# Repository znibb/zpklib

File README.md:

# Znibb's Personal Kicad LIBrary

## Table of Contents <!-- omit from toc -->
- [1. Description](#1-description)
- [2. Setup](#2-setup)
  - [2.1. Inventree](#21-inventree)
  - [2.2. Kicad](#22-kicad)
- [3. Usage](#3-usage)
  - [3.1. Helper scripts](#31-helper-scripts)
  - [3.2. Bulk update Inventree](#32-bulk-update-inventree)
  - [3.3. Adding components to categories](#33-adding-components-to-categories)
  - [3.4. Assemblies](#34-assemblies)
  - [3.5. Releasing a project](#35-releasing-a-project)
  - [3.6. Customizing category symbols](#36-customizing-category-symbols)
- [4. KiCad layer specific usage](#4-kicad-layer-specific-usage)
- [5. EMS Capabilities](#5-ems-capabilities)

## 1. Description
The name of your KiCad symbol libraries will be `LIBRARY_FILE_NAME - TOP_LEVEL_CATEGORY/SUBCATEGORY`, meaning that if your setup is using:

    - Library file name: zpklib.kicad_httplib
    - Inventree top level category name: kicad-parts
    - Subcategory: Resistor

your resistors will show up under a symbol library named `zpklib - kicad-parts/Resistor`

## 2. Setup
### 2.1. Inventree
1. Log into the Inventree web UI and access the Django admin panel by appending `/admin/` to the URL (NOTE the trailing forward slash)
1. Scroll down to `USERS->API Tokens`, click it and then click `ADD API TOKEN +`
1. Take nto of the `Key`, select which `User` the key is for and click `SAVE`

### 2.2. Kicad
1. Create a python venv and install the required packages: `./setup-venv.sh`
1. Create the httplib file: `setup-inventree-httplib.sh`
1. Check that the Inventree server is reachable: `./check_inventree_connection.py`
1. Open the KiCad main window, go to `Preferences->Configure Paths...`
1. Add an `Environment Variable` called `ZPKLIB_DIR` that points to your local library path and click `OK`
1. Go to `Preferences->Manage Symbol Libraries...` and click `Add existing->HTTP (.kicad_httplib)`
1. Select `zpklib.kicad_httplib` and click `Open`

## 3. Usage
### 3.1. Helper scripts
| Name | Usage |
| :--- | :---- |
| check_inventree_connection.py | Verify if httplib is setup correctly |
| create_part.py | Create new Part based on existing component structure |
| next_assembly_ipn.py | Create new EA Part with next IPN in series |
| patch_inventree_structure.py | Compares current `kicad-parts` category state with inventree_structure.yaml and patches the difference in Inventree |
| release_project.py | Handles creation of git tag, github release and upload of relevant assets to said release |
| setup-inventree-httplib.sh | Creates the httplib file used by Kicad to access Inventree |
| setup-venv.sh | Creates a python venv and installs the modules specified in `requirements.txt` |
| update_assembly.py | Update the Inventree Part for the Electronic Assembly |

### 3.2. Bulk update Inventree
1. Source the venv: `. .venv/bin/activate`
1. Analyze the contents of `inventree_structure.yaml` 
1. Applying the structure by running: `./patch_inventree_structure.py`  

### 3.3. Adding components to categories
1. Source the venv: `. .venv/bin/activate`
1. Run `./create_part.py`

### 3.4. Assemblies
1. Source the venv: `. .venv/bin/activate`
1. Reserve an assembly IPN (can be run from any directory): `./next_assembly_ipn.py`. It prompts for the assembly name, creates the part under `electronic-assemblies` and prints the IPN and a link to it
1. In KiCad, go to `Schematic Setup->Project->Text Variables` and add `PART_NUMBER` with the printed IPN
1. Generate the production files, then upload the assembly information (BOM, revision, description and image) to that IPN: `./update_assembly.py PROJECT_DIR`

### 3.5. Releasing a project
1. In the Kicad project, set the `VERSION` and `RELEASE_DATE` text variables, add a `## vX.Y.Z` section to `CHANGELOG.md`, run the production jobset, then commit and push
1. Create the git tag and GitHub release and upload the production files: `./release_project.py PROJECT_DIR`

The script needs `git` and an authenticated `gh`. It aborts if the working tree is dirty, HEAD isn't pushed, or any file name's `_vX.Y.Z_` doesn't match `VERSION`. If the tag or release already exists you are asked before it is overwritten. The uploaded files are set by `FILE_PATTERNS` at the top of the script, and the release notes are the matching `CHANGELOG.md` section.

### 3.6. Customizing category symbols
Kicad handles the default symbol fields `reference, value, footprint, datasheet, description, keywords` in it's own batch, showing `reference` and `value` while hiding the rest by default.  

To hide any of the default fields add:  
```
kicad:
    hide_fields: "FIELD_NAME"
```
to that category in `inventree_structure.yaml`.

The rest of the symbol fields are considered "extra" fields. To make an extra field visible on the symbol add:
```
kivad:
    show_extra_fields: "FIELD_NAME"
```
to that category in `inventree_structure.yaml`.

## 4. KiCad layer specific usage
| Layer | Usage |
| :---- | :---- |
| User.Drawings | PCB/feature dimensions |
| User.Comments | Footprint-specific notes, connector protrusion etc. |
| User.1 / PCB.Comments | PCB comments, stackup details, impedances etc. |

## 5. EMS Capabilities
EMS:
- [JLCPCB](docs/capabilities_JLCPCB.md)

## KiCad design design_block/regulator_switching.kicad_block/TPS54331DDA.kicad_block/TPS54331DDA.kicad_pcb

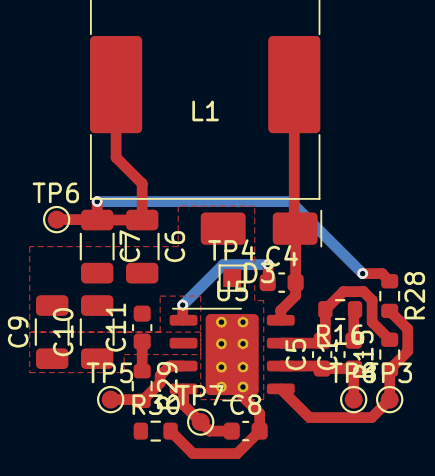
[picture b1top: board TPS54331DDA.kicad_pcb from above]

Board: 4 copper layers, 23 parts (0 on the bottom side), 10 nets.

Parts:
C1: 1n; C_0603_1608Metric
C4: 100n; C_0603_1608Metric
C5: 47p; C_0603_1608Metric
C6, C7: 47u; C_1206_3216Metric
C8: 12n; C_0603_1608Metric
C9, C10: 4.7u; C_1206_3216Metric
C11: 10n; C_0603_1608Metric
D3: B340A-E3-61T; D_SMA
L1: 6.8u; L_12.5x12.5mm_H6.5mm
R15: 3.24k; R_0603_1608Metric
R16: 29.4k; R_0603_1608Metric
R28: 10k; R_0603_1608Metric
R29: 33.2k; R_0603_1608Metric
R30: 8.45k; R_0603_1608Metric
TP3: 3V3_Vsense; TestPoint_Round_D1.0mm
TP4: GND; TestPoint_Square_1.0x1.0mm
TP5: 3V3_EN; TestPoint_Round_D1.0mm
TP6: 3V3; TestPoint_Round_D1.0mm
TP7: 3V3_SS; TestPoint_Round_D1.0mm
TP8: 3V3_COMP; TestPoint_Round_D1.0mm
U5: TPS54331DDAR; SO-8-PowerSOIC_ThermalVias

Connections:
/Regulator 3V3/+3V3: C6.1, C7.1, L1.2, R28.1, TP6.1 (1_1)
/Regulator 3V3/COMP: C1.1, C5.1, TP8.1 (1_1), U5.6 (COMP)
/Regulator 3V3/EN: R29.2, R30.1, TP5.1 (1_1), U5.3 (EN)
/Regulator 3V3/SS: C8.1, TP7.1 (1_1), U5.4 (SS)
/Regulator 3V3/SW: C4.2, D3.1 (K), L1.1, U5.8 (PH)
/Regulator 3V3/V_{IN}: C9.1, C10.1, C11.1, R29.1, U5.2 (V_{IN})
/Regulator 3V3/V_{SENSE}: R15.1, R28.2, TP3.1 (1_1), U5.5 (V_{SENSE})
GND: C5.2, C6.2, C7.2, C8.2, C9.2, C10.2, C11.2, D3.2 (A), R15.2, R16.2, R30.2, TP4.1 (1_1), U5.7 (GND), U5.9 (EPAD)
unnamed: C1.2, R16.1
unnamed: C4.1, U5.1 (BOOT)

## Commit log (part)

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2026-03-12 Set up .gitignore
2026-03-15 Added 0201->1210 footprints for resistors, capacitors and inductors
2026-03-15 Added basic symbols for resistors, capacitors and inductors
2026-03-15 Added tools for local dev instance of inventree
2026-03-15 Updated gitignore
2026-03-15 Updated documentation, WIP
2026-04-01 Deleted obsolete local httplib file
2026-04-01 Added SOIC-16W_7.5x10.3mm_P1.27mm footprint
2026-04-02 Added a generic Symbol parameter handle categories without default symbols
2026-04-02 Added Sensor category
2026-04-02 Changed URL handling to allow handling of other cases than a straight up pdf file
2026-04-04 Added IPC-7354 reference document
2026-04-04 Added Switch category
2026-04-04 Added C&K PTS645VH83 mom push switch
2026-04-04 Added option to enter Value as blank to re-use MPN
2026-04-05 Added LED category
2026-04-05 Added Kingbright WP934SA LED
2026-04-05 Removed obsolute dev code regarding Symbol map settings
2026-04-05 Removed obsolete dev script
2026-04-05 Moved temperature parameters to top-level
2026-04-05 Changed Switch category icon to be different from the Relay one
2026-04-05 Added Relay category
2026-04-05 Added Omron G5Q-1A4 relay
2026-04-05 Renamed patch script
2026-04-05 Fixed IPN detection to be global to all categories
2026-04-05 Added diode category
2026-04-05 Fixed symbol error in C20 receptacle
2026-04-05 Added dev patch of serializer to handle hiding ref des for power symbols
2026-04-05 Added power symbol category
2026-04-05 Added Fuse and FuseHolder categories
2026-04-05 Added missing fuse parameters
2026-04-05 Set up hiding of default fields and showing of extra fields with per-category parameters
2026-04-05 Added Omron G2RL-1A-E relay
2026-04-05 Added Transistor category
2026-04-05 Changed patch script to sum step 3 changes at the end of the step
2026-04-06 Removed autoplace property of VoltageRating field for Capacitor category
2026-04-06 Fixed error in Transistor packages selection list
2026-04-06 Enabled showing of Case and VoltageRating fields in Capacitor symbols
2026-04-06 Changed reporting to group unchanged entities and list changed entities summarily at the end of each step
2026-04-06 Enforcing inheritance of category parameters
2026-04-06 Updating existing THT footprints to be flagged as THT
2026-04-06 Added Recom RAC05E-KT footprint and symbol
2026-04-06 Added PowerModule category
2026-04-06 Removed autoplace property from PowerModule Power field
2026-04-06 Consolidated PowerDecimal and PowerFractional parameters into simply Power
2026-04-06 Added optocoupler symbols and footprint
2026-04-06 Added SO-4_4.4x3.6mm_P2.54mm footprint
2026-04-06 Improved ACS37800 symbol disposition
2026-04-06 Separated optocoupler symbols into specific AC and DC versions
2026-04-06 Created Isolator category
2026-04-06 Remvoed PowerSymbol category, will be handled directly in symbol lib instead
2026-04-06 Revamped power symbol library to bypass Inventree and work locally instead
2026-04-06 Fixed indentation issue introduced when removing PowerSymbol category
2026-04-06 Fixed error in power symbol value
2026-04-06 Added testpoints to library
2026-04-06 Added NetTies
2026-04-06 Changed square test point value to be GND by default
2026-04-06 Added switching regulator category
2026-04-06 Added switching regulator symbol and footprint
2026-04-06 Fixed error with switching regulator packages
2026-04-06 Updated parameters for polarized capacitors
2026-04-06 Added C_2917_7343Metric footprint
2026-04-06 Flipped rectifier diode symbol to have pin 1 to the left
2026-04-06 Added SMA diode package
2026-04-06 Added schottky diode category
2026-04-07 Fixed MOSFET symbol pin naming
2026-04-07 Fixed pin swap mistake in TPS54331 symbol
2026-04-07 Fixed pad naming in Kingbright LED footprint
2026-04-07 Added diode polarity indicator to SMA footprint
2026-04-07 Added 12.5x12.5mm H6.5mm inductor footprint
2026-04-07 Added TPS54331DDA design block
2026-04-07 Added Kicad template project
2026-04-07 Added EMS capabilities section to README
2026-04-08 Added 5mm wide net tie
2026-04-08 Added 4-channel optocoupler symbols and footprint
2026-04-08 Added polarity indication on SOD-323 footprint
2026-04-08 Adjusted pad sizes on SMDIP-8 footprint
2026-04-08 Added helper line indicating mid point between switched net and coil net
2026-04-08 Removed _power_ property on IP+ and IP- pins of ACS37800, were making net names global
2026-04-08 Added _Keep Upright_ property to AC-outlet footprints
2026-04-08 Enabled _Keep upright_ on Recom-RAC05E footprint
2026-04-08 Updated README with instructions for using env var for library paths
2026-04-08 Added RJ45 connector
2026-04-08 Added mounting hole category
2026-04-09 Created InterfaceEthernet category
2026-04-09 Restructured structure file to follow alphabetical order better
2026-04-09 Made JTAG pin order more intuitive
2026-04-09 Added ST Microcontroller category
2026-04-09 Updated structure to allow package selectionlists to source from a list of footprint libraries
2026-04-09 Added JST GH BM footprints (02-15)
2026-04-09 Added JST GH SM footprints (02-15)
2026-04-09 Added JST XH-B footprints (02-16,20)
2026-04-09 Added JST XH-S footprints (02-16)
2026-04-09 Added generic 01x[02-20] connector symbols
2026-04-09 Added JST connector footprints to connector selectionlist
2026-04-09 Added jumper category
2026-04-09 Added fan connector category
2026-04-09 Fixed parameter naming typo
2026-04-10 Changed default display parameter from ValueStandard to ValueAlternate
2026-04-10 Added TagConnect connectors
2026-04-11 Added crystal category
2026-04-11 Added PinHeader category
2026-04-11 Added part URL output to the creation script
2026-04-11 Added push switch footprint
2026-04-11 Updated pin header and switch categories
2026-04-11 Added dedicated 01x02 pin header symbol
2026-04-11 Added crystal oscillator to crystal category
2026-04-11 Updated eth phy symbol for easier schematic design
2026-04-11 Changed datasheet download timeout from 60 s to 10 s
2026-04-11 Added USB-C 2.0 receptacle
2026-04-11 Added Power Protection category
2026-04-11 Made power symbols derive from a master symbol
2026-04-11 Fixed misconfigured pin on crystal oscillator symbol
2026-04-11 Improved ETH PHY symbol layout
2026-04-11 Improved STM32F407 symbol layout
2026-04-11 Shrunk SW-Push symbol pins
2026-04-11 Fixed missing/wrong 3D-models
2026-04-11 USB-C 2.0 symbol trim
2026-04-11 Updated USB ESD device symbol
2026-04-11 Added more LED package options
2026-04-11 Fixed parameter mapping for LED x1 symbol
2026-04-11 Fixed naming error on LED chip footprints
2026-04-11 Removed MP pad names in JST GH footprints
2026-04-11 Adjusted STM32F407 symbol
2026-04-12 Changed power symbols to be local rather than global
2026-04-12 Added TMP1075 temperature sensor
2026-04-12 Modified STM32F407 symbol
2026-04-12 Added more diode packages
2026-04-12 Corrected symbol pin electrical types
2026-04-12 Added _Keep upright_ property to some labels that were missing it
2026-04-13 Changed PE GND symbol pin typ to _power in_ so that it drives net name
2026-04-13 Fixed LED 0603 footprint
2026-04-13 Fixed footprint filter
2026-04-13 Added autoplacement on switch fields
2026-04-14 Added _keep upright_ to text labels
2026-04-19 Footprint adjustments
2026-04-22 Made thermal vias connect solid instead of thermal relief
2026-04-22 Minor footprint and symbol tweaks
2026-04-22 Added layer usage documentation
2026-04-23 Started implementing Production Files output jobset
2026-04-24 Added provisions for PCBWAY output
2026-04-24 Generate only Digikey output (BOM) for now
2026-04-24 Added pandas to requirements to enable execution of convert-bom script
2026-04-24 Added support script for uploading a PCBA BOM and creating an electronic assembly out of it
2026-04-25 Changed gerber output to not use Protel file endings
2026-04-25 Updated comment wording
2026-04-25 Fixed component creation script picking up categories outside of kicad-parts
2026-04-25 Added PCB rendering image outputs
2026-04-26 Fixed duplicate Render outputs
2026-04-26 Re-fixed component creation script since it wasn't picking up any categories at all
2026-04-26 Updated assembly creation script to auto-detect most required info
2026-05-06 Refactored create_assembly.py so it's meant to be ran from the lib dir with the project dir as argument
